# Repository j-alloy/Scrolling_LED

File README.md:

# Scrolling_LED
Simple KiCAD schemtic of a scrolling LED

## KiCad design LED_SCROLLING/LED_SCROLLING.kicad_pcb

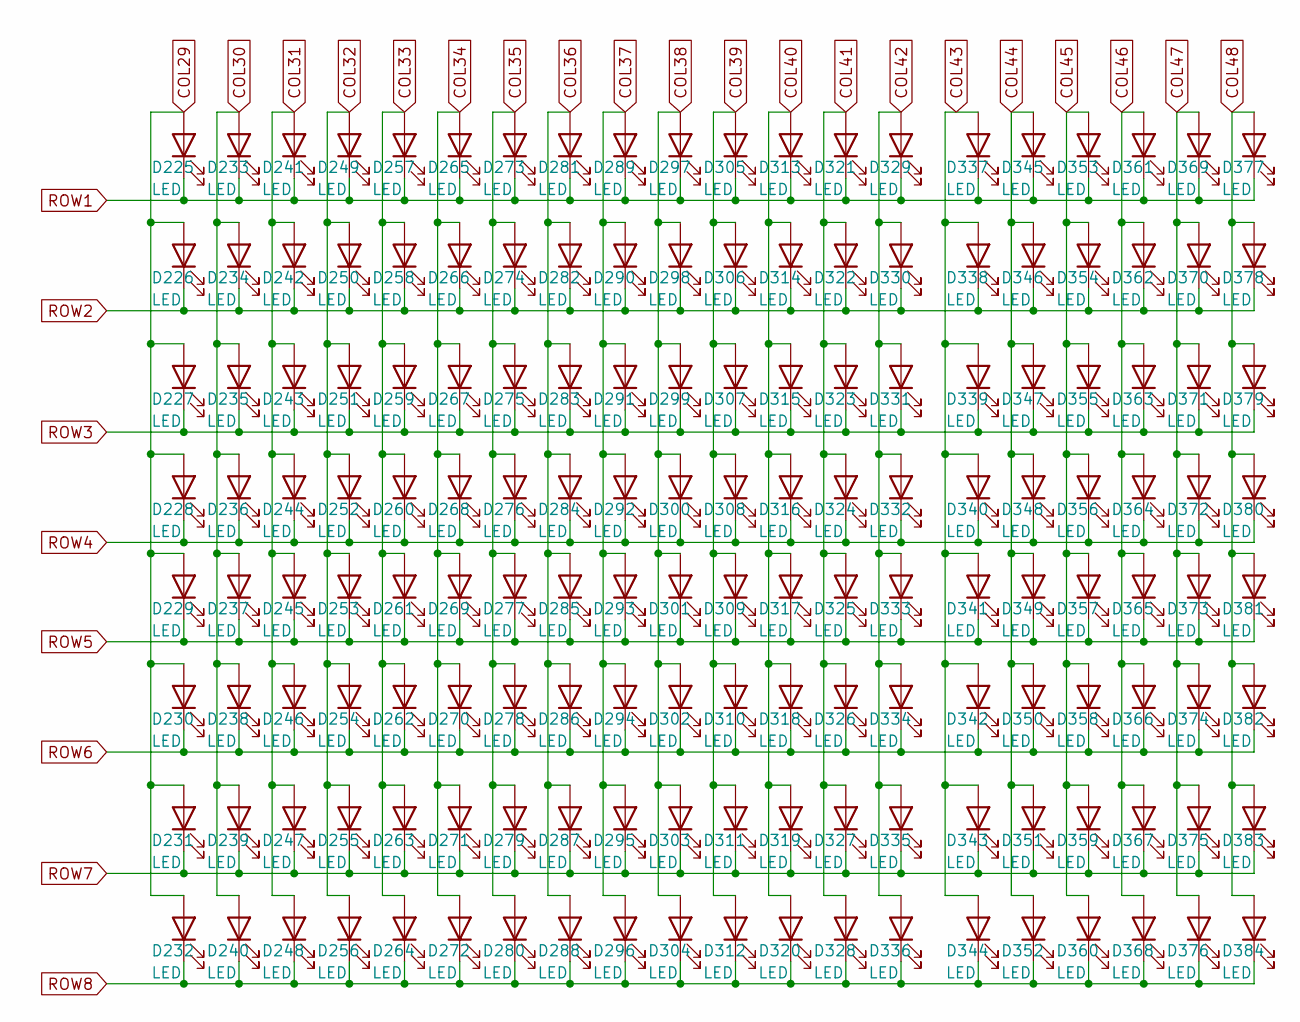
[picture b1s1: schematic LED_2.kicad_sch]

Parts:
D225, D226, D227, D228, D229, D230, D231, D232, D233, D234, D235, D236, D237, D238, D239, D240, D241, D242, D243, D244, D245, D246, D247, D248, D249, D250, D251, D252, D253, D254, D255, D256, D257, D258, D259, D260, D261, D262, D263, D264, D265, D266, D267, D268, D269, D270, D271, D272, D273, D274, D275, D276, D277, D278, D279, D280, D281, D282, D283, D284, D285, D286, D287, D288, D289, D290, D291, D292, D293, D294, D295, D296, D297, D298, D299, D300, D301, D302, D303, D304, D305, D306, D307, D308, D309, D310, D311, D312, D313, D314, D315, D316, D317, D318, D319, D320, D321, D322, D323, D324, D325, D326, D327, D328, D329, D330, D331, D332, D333, D334, D335, D336, D337, D338, D339, D340, D341, D342, D343, D344, D345, D346, D347, D348, D349, D350, D351, D352, D353, D354, D355, D356, D357, D358, D359, D360, D361, D362, D363, D364, D365, D366, D367, D368, D369, D370, D371, D372, D373, D374, D375, D376, D377, D378, D379, D380, D381, D382, D383, D384: LED; LED_0805_2012Metric

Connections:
COL29: D225.2 (A), D226.2 (A), D227.2 (A), D228.2 (A), D229.2 (A), D230.2 (A), D231.2 (A), D232.2 (A); also elsewhere on the board
COL30: D233.2 (A), D234.2 (A), D235.2 (A), D236.2 (A), D237.2 (A), D238.2 (A), D239.2 (A), D240.2 (A); also elsewhere on the board
COL31: D241.2 (A), D242.2 (A), D243.2 (A), D244.2 (A), D245.2 (A), D246.2 (A), D247.2 (A), D248.2 (A); also elsewhere on the board
COL32: D249.2 (A), D250.2 (A), D251.2 (A), D252.2 (A), D253.2 (A), D254.2 (A), D255.2 (A), D256.2 (A); also elsewhere on the board
COL33: D257.2 (A), D258.2 (A), D259.2 (A), D260.2 (A), D261.2 (A), D262.2 (A), D263.2 (A), D264.2 (A); also elsewhere on the board
COL34: D265.2 (A), D266.2 (A), D267.2 (A), D268.2 (A), D269.2 (A), D270.2 (A), D271.2 (A), D272.2 (A); also elsewhere on the board
COL35: D273.2 (A), D274.2 (A), D275.2 (A), D276.2 (A), D277.2 (A), D278.2 (A), D279.2 (A), D280.2 (A); also elsewhere on the board
COL36: D281.2 (A), D282.2 (A), D283.2 (A), D284.2 (A), D285.2 (A), D286.2 (A), D287.2 (A), D288.2 (A); also elsewhere on the board
COL37: D289.2 (A), D290.2 (A), D291.2 (A), D292.2 (A), D293.2 (A), D294.2 (A), D295.2 (A), D296.2 (A); also elsewhere on the board
COL38: D297.2 (A), D298.2 (A), D299.2 (A), D300.2 (A), D301.2 (A), D302.2 (A), D303.2 (A), D304.2 (A); also elsewhere on the board
COL39: D305.2 (A), D306.2 (A), D307.2 (A), D308.2 (A), D309.2 (A), D310.2 (A), D311.2 (A), D312.2 (A); also elsewhere on the board
COL40: D313.2 (A), D314.2 (A), D315.2 (A), D316.2 (A), D317.2 (A), D318.2 (A), D319.2 (A), D320.2 (A); also elsewhere on the board
COL41: D321.2 (A), D322.2 (A), D323.2 (A), D324.2 (A), D325.2 (A), D326.2 (A), D327.2 (A), D328.2 (A); also elsewhere on the board
COL42: D329.2 (A), D330.2 (A), D331.2 (A), D332.2 (A), D333.2 (A), D334.2 (A), D335.2 (A), D336.2 (A); also elsewhere on the board
COL43: D337.2 (A), D338.2 (A), D339.2 (A), D340.2 (A), D341.2 (A), D342.2 (A), D343.2 (A), D344.2 (A); also elsewhere on the board
COL44: D345.2 (A), D346.2 (A), D347.2 (A), D348.2 (A), D349.2 (A), D350.2 (A), D351.2 (A), D352.2 (A); also elsewhere on the board
COL45: D353.2 (A), D354.2 (A), D355.2 (A), D356.2 (A), D357.2 (A), D358.2 (A), D359.2 (A), D360.2 (A); also elsewhere on the board
COL46: D361.2 (A), D362.2 (A), D363.2 (A), D364.2 (A), D365.2 (A), D366.2 (A), D367.2 (A), D368.2 (A); also elsewhere on the board
COL47: D369.2 (A), D370.2 (A), D371.2 (A), D372.2 (A), D373.2 (A), D374.2 (A), D375.2 (A), D376.2 (A); also elsewhere on the board
COL48: D377.2 (A), D378.2 (A), D379.2 (A), D380.2 (A), D381.2 (A), D382.2 (A), D383.2 (A), D384.2 (A); also elsewhere on the board
ROW1: D225.1 (K), D233.1 (K), D241.1 (K), D249.1 (K), D257.1 (K), D265.1 (K), D273.1 (K), D281.1 (K), D289.1 (K), D297.1 (K), D305.1 (K), D313.1 (K), D321.1 (K), D329.1 (K), D337.1 (K), D345.1 (K), D353.1 (K), D361.1 (K), D369.1 (K), D377.1 (K); also elsewhere on the board
ROW2: D226.1 (K), D234.1 (K), D242.1 (K), D250.1 (K), D258.1 (K), D266.1 (K), D274.1 (K), D282.1 (K), D290.1 (K), D298.1 (K), D306.1 (K), D314.1 (K), D322.1 (K), D330.1 (K), D338.1 (K), D346.1 (K), D354.1 (K), D362.1 (K), D370.1 (K), D378.1 (K); also elsewhere on the board
ROW3: D227.1 (K), D235.1 (K), D243.1 (K), D251.1 (K), D259.1 (K), D267.1 (K), D275.1 (K), D283.1 (K), D291.1 (K), D299.1 (K), D307.1 (K), D315.1 (K), D323.1 (K), D331.1 (K), D339.1 (K), D347.1 (K), D355.1 (K), D363.1 (K), D371.1 (K), D379.1 (K); also elsewhere on the board
ROW4: D228.1 (K), D236.1 (K), D244.1 (K), D252.1 (K), D260.1 (K), D268.1 (K), D276.1 (K), D284.1 (K), D292.1 (K), D300.1 (K), D308.1 (K), D316.1 (K), D324.1 (K), D332.1 (K), D340.1 (K), D348.1 (K), D356.1 (K), D364.1 (K), D372.1 (K), D380.1 (K); also elsewhere on the board
ROW5: D229.1 (K), D237.1 (K), D245.1 (K), D253.1 (K), D261.1 (K), D269.1 (K), D277.1 (K), D285.1 (K), D293.1 (K), D301.1 (K), D309.1 (K), D317.1 (K), D325.1 (K), D333.1 (K), D341.1 (K), D349.1 (K), D357.1 (K), D365.1 (K), D373.1 (K), D381.1 (K); also elsewhere on the board
ROW6: D230.1 (K), D238.1 (K), D246.1 (K), D254.1 (K), D262.1 (K), D270.1 (K), D278.1 (K), D286.1 (K), D294.1 (K), D302.1 (K), D310.1 (K), D318.1 (K), D326.1 (K), D334.1 (K), D342.1 (K), D350.1 (K), D358.1 (K), D366.1 (K), D374.1 (K), D382.1 (K); also elsewhere on the board
ROW7: D231.1 (K), D239.1 (K), D247.1 (K), D255.1 (K), D263.1 (K), D271.1 (K), D279.1 (K), D287.1 (K), D295.1 (K), D303.1 (K), D311.1 (K), D319.1 (K), D327.1 (K), D335.1 (K), D343.1 (K), D351.1 (K), D359.1 (K), D367.1 (K), D375.1 (K), D383.1 (K); also elsewhere on the board
ROW8: D232.1 (K), D240.1 (K), D248.1 (K), D256.1 (K), D264.1 (K), D272.1 (K), D280.1 (K), D288.1 (K), D296.1 (K), D304.1 (K), D312.1 (K), D320.1 (K), D328.1 (K), D336.1 (K), D344.1 (K), D352.1 (K), D360.1 (K), D368.1 (K), D376.1 (K), D384.1 (K); also elsewhere on the board

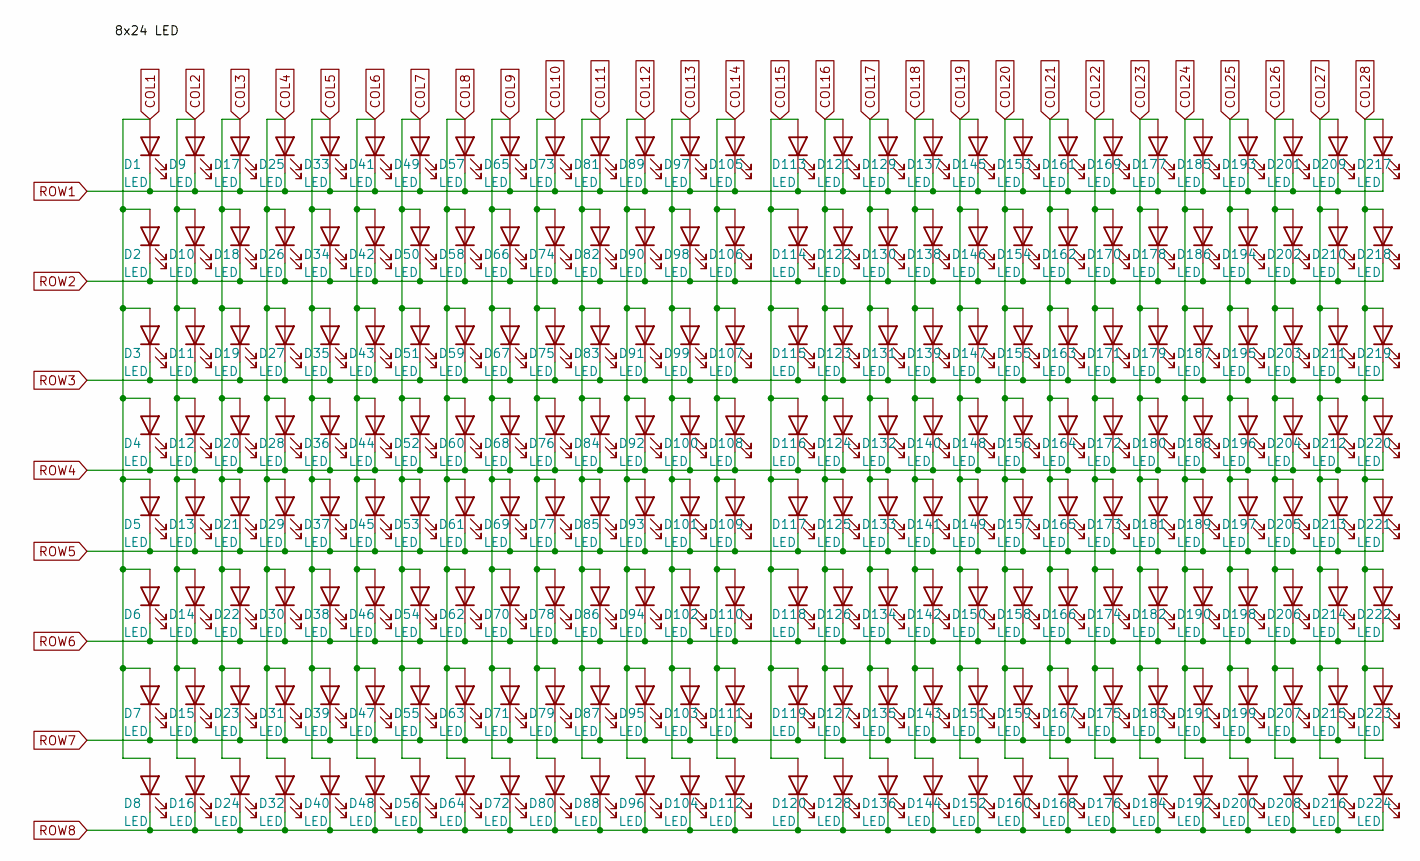
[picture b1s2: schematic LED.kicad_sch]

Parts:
D1, D2, D3, D4, D5, D6, D7, D8, D9, D10, D11, D12, D13, D14, D15, D16, D17, D18, D19, D20, D21, D22, D23, D24, D25, D26, D27, D28, D29, D30, D31, D32, D33, D34, D35, D36, D37, D38, D39, D40, D41, D42, D43, D44, D45, D46, D47, D48, D49, D50, D51, D52, D53, D54, D55, D56, D57, D58, D59, D60, D61, D62, D63, D64, D65, D66, D67, D68, D69, D70, D71, D72, D73, D74, D75, D76, D77, D78, D79, D80, D81, D82, D83, D84, D85, D86, D87, D88, D89, D90, D91, D92, D93, D94, D95, D96, D97, D98, D99, D100, D101, D102, D103, D104, D105, D106, D107, D108, D109, D110, D111, D112, D113, D114, D115, D116, D117, D118, D119, D120, D121, D122, D123, D124, D125, D126, D127, D128, D129, D130, D131, D132, D133, D134, D135, D136, D137, D138, D139, D140, D141, D142, D143, D144, D145, D146, D147, D148, D149, D150, D151, D152, D153, D154, D155, D156, D157, D158, D159, D160, D161, D162, D163, D164, D165, D166, D167, D168, D169, D170, D171, D172, D173, D174, D175, D176, D177, D178, D179, D180, D181, D182, D183, D184, D185, D186, D187, D188, D189, D190, D191, D192, D193, D194, D195, D196, D197, D198, D199, D200, D201, D202, D203, D204, D205, D206, D207, D208, D209, D210, D211, D212, D213, D214, D215, D216, D217, D218, D219, D220, D221, D222, D223, D224: LED; LED_0805_2012Metric

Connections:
COL1: D1.2 (A), D2.2 (A), D3.2 (A), D4.2 (A), D5.2 (A), D6.2 (A), D7.2 (A), D8.2 (A); also elsewhere on the board
COL2: D9.2 (A), D10.2 (A), D11.2 (A), D12.2 (A), D13.2 (A), D14.2 (A), D15.2 (A), D16.2 (A); also elsewhere on the board
COL3: D17.2 (A), D18.2 (A), D19.2 (A), D20.2 (A), D21.2 (A), D22.2 (A), D23.2 (A), D24.2 (A); also elsewhere on the board
COL4: D25.2 (A), D26.2 (A), D27.2 (A), D28.2 (A), D29.2 (A), D30.2 (A), D31.2 (A), D32.2 (A); also elsewhere on the board
COL5: D33.2 (A), D34.2 (A), D35.2 (A), D36.2 (A), D37.2 (A), D38.2 (A), D39.2 (A), D40.2 (A); also elsewhere on the board
COL6: D41.2 (A), D42.2 (A), D43.2 (A), D44.2 (A), D45.2 (A), D46.2 (A), D47.2 (A), D48.2 (A); also elsewhere on the board
COL7: D49.2 (A), D50.2 (A), D51.2 (A), D52.2 (A), D53.2 (A), D54.2 (A), D55.2 (A), D56.2 (A); also elsewhere on the board
COL8: D57.2 (A), D58.2 (A), D59.2 (A), D60.2 (A), D61.2 (A), D62.2 (A), D63.2 (A), D64.2 (A); also elsewhere on the board
COL9: D65.2 (A), D66.2 (A), D67.2 (A), D68.2 (A), D69.2 (A), D70.2 (A), D71.2 (A), D72.2 (A); also elsewhere on the board
COL10: D73.2 (A), D74.2 (A), D75.2 (A), D76.2 (A), D77.2 (A), D78.2 (A), D79.2 (A), D80.2 (A); also elsewhere on the board
COL11: D81.2 (A), D82.2 (A), D83.2 (A), D84.2 (A), D85.2 (A), D86.2 (A), D87.2 (A), D88.2 (A); also elsewhere on the board
COL12: D89.2 (A), D90.2 (A), D91.2 (A), D92.2 (A), D93.2 (A), D94.2 (A), D95.2 (A), D96.2 (A); also elsewhere on the board
COL13: D97.2 (A), D98.2 (A), D99.2 (A), D100.2 (A), D101.2 (A), D102.2 (A), D103.2 (A), D104.2 (A); also elsewhere on the board
COL14: D105.2 (A), D106.2 (A), D107.2 (A), D108.2 (A), D109.2 (A), D110.2 (A), D111.2 (A), D112.2 (A); also elsewhere on the board
COL15: D113.2 (A), D114.2 (A), D115.2 (A), D116.2 (A), D117.2 (A), D118.2 (A), D119.2 (A), D120.2 (A); also elsewhere on the board
COL16: D121.2 (A), D122.2 (A), D123.2 (A), D124.2 (A), D125.2 (A), D126.2 (A), D127.2 (A), D128.2 (A); also elsewhere on the board
COL17: D129.2 (A), D130.2 (A), D131.2 (A), D132.2 (A), D133.2 (A), D134.2 (A), D135.2 (A), D136.2 (A); also elsewhere on the board
COL18: D137.2 (A), D138.2 (A), D139.2 (A), D140.2 (A), D141.2 (A), D142.2 (A), D143.2 (A), D144.2 (A); also elsewhere on the board
COL19: D145.2 (A), D146.2 (A), D147.2 (A), D148.2 (A), D149.2 (A), D150.2 (A), D151.2 (A), D152.2 (A); also elsewhere on the board
COL20: D153.2 (A), D154.2 (A), D155.2 (A), D156.2 (A), D157.2 (A), D158.2 (A), D159.2 (A), D160.2 (A); also elsewhere on the board
COL21: D161.2 (A), D162.2 (A), D163.2 (A), D164.2 (A), D165.2 (A), D166.2 (A), D167.2 (A), D168.2 (A); also elsewhere on the board
COL22: D169.2 (A), D170.2 (A), D171.2 (A), D172.2 (A), D173.2 (A), D174.2 (A), D175.2 (A), D176.2 (A); also elsewhere on the board
COL23: D177.2 (A), D178.2 (A), D179.2 (A), D180.2 (A), D181.2 (A), D182.2 (A), D183.2 (A), D184.2 (A); also elsewhere on the board
COL24: D185.2 (A), D186.2 (A), D187.2 (A), D188.2 (A), D189.2 (A), D190.2 (A), D191.2 (A), D192.2 (A); also elsewhere on the board
COL25: D193.2 (A), D194.2 (A), D195.2 (A), D196.2 (A), D197.2 (A), D198.2 (A), D199.2 (A), D200.2 (A); also elsewhere on the board
COL26: D201.2 (A), D202.2 (A), D203.2 (A), D204.2 (A), D205.2 (A), D206.2 (A), D207.2 (A), D208.2 (A); also elsewhere on the board
COL27: D209.2 (A), D210.2 (A), D211.2 (A), D212.2 (A), D213.2 (A), D214.2 (A), D215.2 (A), D216.2 (A); also elsewhere on the board
COL28: D217.2 (A), D218.2 (A), D219.2 (A), D220.2 (A), D221.2 (A), D222.2 (A), D223.2 (A), D224.2 (A); also elsewhere on the board
ROW1: D1.1 (K), D9.1 (K), D17.1 (K), D25.1 (K), D33.1 (K), D41.1 (K), D49.1 (K), D57.1 (K), D65.1 (K), D73.1 (K), D81.1 (K), D89.1 (K), D97.1 (K), D105.1 (K), D113.1 (K), D121.1 (K), D129.1 (K), D137.1 (K), D145.1 (K), D153.1 (K), D161.1 (K), D169.1 (K), D177.1 (K), D185.1 (K), D193.1 (K), D201.1 (K), D209.1 (K), D217.1 (K); also elsewhere on the board
ROW2: D2.1 (K), D10.1 (K), D18.1 (K), D26.1 (K), D34.1 (K), D42.1 (K), D50.1 (K), D58.1 (K), D66.1 (K), D74.1 (K), D82.1 (K), D90.1 (K), D98.1 (K), D106.1 (K), D114.1 (K), D122.1 (K), D130.1 (K), D138.1 (K), D146.1 (K), D154.1 (K), D162.1 (K), D170.1 (K), D178.1 (K), D186.1 (K), D194.1 (K), D202.1 (K), D210.1 (K), D218.1 (K); also elsewhere on the board
ROW3: D3.1 (K), D11.1 (K), D19.1 (K), D27.1 (K), D35.1 (K), D43.1 (K), D51.1 (K), D59.1 (K), D67.1 (K), D75.1 (K), D83.1 (K), D91.1 (K), D99.1 (K), D107.1 (K), D115.1 (K), D123.1 (K), D131.1 (K), D139.1 (K), D147.1 (K), D155.1 (K), D163.1 (K), D171.1 (K), D179.1 (K), D187.1 (K), D195.1 (K), D203.1 (K), D211.1 (K), D219.1 (K); also elsewhere on the board
ROW4: D4.1 (K), D12.1 (K), D20.1 (K), D28.1 (K), D36.1 (K), D44.1 (K), D52.1 (K), D60.1 (K), D68.1 (K), D76.1 (K), D84.1 (K), D92.1 (K), D100.1 (K), D108.1 (K), D116.1 (K), D124.1 (K), D132.1 (K), D140.1 (K), D148.1 (K), D156.1 (K), D164.1 (K), D172.1 (K), D180.1 (K), D188.1 (K), D196.1 (K), D204.1 (K), D212.1 (K), D220.1 (K); also elsewhere on the board
ROW5: D5.1 (K), D13.1 (K), D21.1 (K), D29.1 (K), D37.1 (K), D45.1 (K), D53.1 (K), D61.1 (K), D69.1 (K), D77.1 (K), D85.1 (K), D93.1 (K), D101.1 (K), D109.1 (K), D117.1 (K), D125.1 (K), D133.1 (K), D141.1 (K), D149.1 (K), D157.1 (K), D165.1 (K), D173.1 (K), D181.1 (K), D189.1 (K), D197.1 (K), D205.1 (K), D213.1 (K), D221.1 (K); also elsewhere on the board
ROW6: D6.1 (K), D14.1 (K), D22.1 (K), D30.1 (K), D38.1 (K), D46.1 (K), D54.1 (K), D62.1 (K), D70.1 (K), D78.1 (K), D86.1 (K), D94.1 (K), D102.1 (K), D110.1 (K), D118.1 (K), D126.1 (K), D134.1 (K), D142.1 (K), D150.1 (K), D158.1 (K), D166.1 (K), D174.1 (K), D182.1 (K), D190.1 (K), D198.1 (K), D206.1 (K), D214.1 (K), D222.1 (K); also elsewhere on the board
ROW7: D7.1 (K), D15.1 (K), D23.1 (K), D31.1 (K), D39.1 (K), D47.1 (K), D55.1 (K), D63.1 (K), D71.1 (K), D79.1 (K), D87.1 (K), D95.1 (K), D103.1 (K), D111.1 (K), D119.1 (K), D127.1 (K), D135.1 (K), D143.1 (K), D151.1 (K), D159.1 (K), D167.1 (K), D175.1 (K), D183.1 (K), D191.1 (K), D199.1 (K), D207.1 (K), D215.1 (K), D223.1 (K); also elsewhere on the board
ROW8: D8.1 (K), D16.1 (K), D24.1 (K), D32.1 (K), D40.1 (K), D48.1 (K), D56.1 (K), D64.1 (K), D72.1 (K), D80.1 (K), D88.1 (K), D96.1 (K), D104.1 (K), D112.1 (K), D120.1 (K), D128.1 (K), D136.1 (K), D144.1 (K), D152.1 (K), D160.1 (K), D168.1 (K), D176.1 (K), D184.1 (K), D192.1 (K), D200.1 (K), D208.1 (K), D216.1 (K), D224.1 (K); also elsewhere on the board

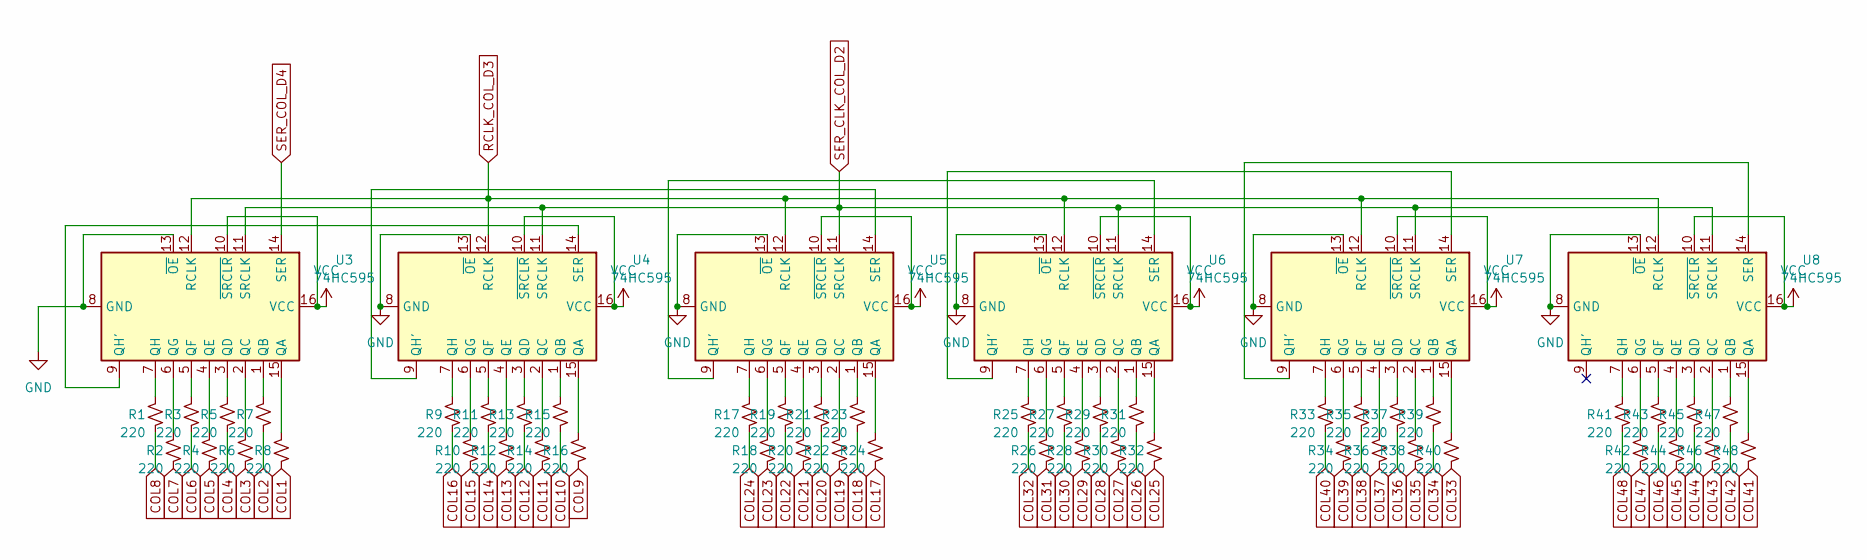
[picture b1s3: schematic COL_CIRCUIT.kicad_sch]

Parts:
R1, R2, R3, R4, R5, R6, R7, R8, R9, R10, R11, R12, R13, R14, R15, R16, R17, R18, R19, R20, R21, R22, R23, R24, R25, R26, R27, R28, R29, R30, R31, R32, R33, R34, R35, R36, R37, R38, R39, R40, R41, R42, R43, R44, R45, R46, R47, R48: 220; R_0805_2012Metric
U3, U4, U5, U6, U7, U8: 74HC595; MC74HC595ADTR2G

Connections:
COL1: R8.2; also elsewhere on the board
COL2: R7.2; also elsewhere on the board
COL3: R6.2; also elsewhere on the board
COL4: R5.2; also elsewhere on the board
COL5: R4.2; also elsewhere on the board
COL6: R3.2; also elsewhere on the board
COL7: R2.2; also elsewhere on the board
COL8: R1.2; also elsewhere on the board
COL9: R16.2; also elsewhere on the board
COL10: R15.2; also elsewhere on the board
COL11: R14.2; also elsewhere on the board
COL12: R13.2; also elsewhere on the board
COL13: R12.2; also elsewhere on the board
COL14: R11.2; also elsewhere on the board
COL15: R10.2; also elsewhere on the board
COL16: R9.2; also elsewhere on the board
COL17: R24.2; also elsewhere on the board
COL18: R23.2; also elsewhere on the board
COL19: R22.2; also elsewhere on the board
COL20: R21.2; also elsewhere on the board
COL21: R20.2; also elsewhere on the board
COL22: R19.2; also elsewhere on the board
COL23: R18.2; also elsewhere on the board
COL24: R17.2; also elsewhere on the board
COL25: R32.2; also elsewhere on the board
COL26: R31.2; also elsewhere on the board
COL27: R30.2; also elsewhere on the board
COL28: R29.2; also elsewhere on the board
COL29: R28.2; also elsewhere on the board
COL30: R27.2; also elsewhere on the board
COL31: R26.2; also elsewhere on the board
COL32: R25.2; also elsewhere on the board
COL33: R40.2; also elsewhere on the board
COL34: R39.2; also elsewhere on the board
COL35: R38.2; also elsewhere on the board
COL36: R37.2; also elsewhere on the board
COL37: R36.2; also elsewhere on the board
COL38: R35.2; also elsewhere on the board
COL39: R34.2; also elsewhere on the board
COL40: R33.2; also elsewhere on the board
COL41: R48.2; also elsewhere on the board
COL42: R47.2; also elsewhere on the board
COL43: R46.2; also elsewhere on the board
COL44: R45.2; also elsewhere on the board
COL45: R44.2; also elsewhere on the board
COL46: R43.2; also elsewhere on the board
COL47: R42.2; also elsewhere on the board
COL48: R41.2; also elsewhere on the board
GND: U3.8 (GND), U3.13 (~OE), U4.8 (GND), U4.13 (~OE), U5.8 (GND), U5.13 (~OE), U6.8 (GND), U6.13 (~OE), U7.8 (GND), U7.13 (~OE), U8.8 (GND), U8.13 (~OE); also elsewhere on the board
unnamed: R1.1, U3.7 (QH)
unnamed: R2.1, U3.6 (QG)
unnamed: R3.1, U3.5 (QF)
unnamed: R4.1, U3.4 (QE)
unnamed: R5.1, U3.3 (QD)
unnamed: R6.1, U3.2 (QC)
unnamed: R7.1, U3.1 (QB)
unnamed: R8.1, U3.15 (QA)
unnamed: R9.1, U4.7 (QH)
unnamed: R10.1, U4.6 (QG)
unnamed: R11.1, U4.5 (QF)
unnamed: R12.1, U4.4 (QE)
unnamed: R13.1, U4.3 (QD)
unnamed: R14.1, U4.2 (QC)
unnamed: R15.1, U4.1 (QB)
unnamed: R16.1, U4.15 (QA)
unnamed: R17.1, U5.7 (QH)
unnamed: R18.1, U5.6 (QG)
unnamed: R19.1, U5.5 (QF)
unnamed: R20.1, U5.4 (QE)
unnamed: R21.1, U5.3 (QD)
unnamed: R22.1, U5.2 (QC)
unnamed: R23.1, U5.1 (QB)
unnamed: R24.1, U5.15 (QA)
unnamed: R25.1, U6.7 (QH)
unnamed: R26.1, U6.6 (QG)
unnamed: R27.1, U6.5 (QF)
unnamed: R28.1, U6.4 (QE)
unnamed: R29.1, U6.3 (QD)
unnamed: R30.1, U6.2 (QC)
unnamed: R31.1, U6.1 (QB)
unnamed: R32.1, U6.15 (QA)
unnamed: R33.1, U7.7 (QH)
unnamed: R34.1, U7.6 (QG)
unnamed: R35.1, U7.5 (QF)
unnamed: R36.1, U7.4 (QE)
unnamed: R37.1, U7.3 (QD)
unnamed: R38.1, U7.2 (QC)
unnamed: R39.1, U7.1 (QB)
unnamed: R40.1, U7.15 (QA)
unnamed: R41.1, U8.7 (QH)
unnamed: R42.1, U8.6 (QG)
unnamed: R43.1, U8.5 (QF)
unnamed: R44.1, U8.4 (QE)
unnamed: R45.1, U8.3 (QD)
unnamed: R46.1, U8.2 (QC)
unnamed: R47.1, U8.1 (QB)
unnamed: R48.1, U8.15 (QA)
unnamed: U3.9 (QH'), U4.14 (SER)
unnamed: U4.9 (QH'), U5.14 (SER)
unnamed: U5.9 (QH'), U6.14 (SER)
unnamed: U6.9 (QH'), U7.14 (SER)
unnamed: U7.9 (QH'), U8.14 (SER)
RCLK_COL_D3: U3.12 (RCLK), U4.12 (RCLK), U5.12 (RCLK), U6.12 (RCLK), U7.12 (RCLK), U8.12 (RCLK)
SER_CLK_COL_D2: U3.11 (SRCLK), U4.11 (SRCLK), U5.11 (SRCLK), U6.11 (SRCLK), U7.11 (SRCLK), U8.11 (SRCLK)
SER_COL_D4: U3.14 (SER)
VCC: U3.10 (~SRCLR), U3.16 (VCC), U4.10 (~SRCLR), U4.16 (VCC), U5.10 (~SRCLR), U5.16 (VCC), U6.10 (~SRCLR), U6.16 (VCC), U7.10 (~SRCLR), U7.16 (VCC), U8.10 (~SRCLR), U8.16 (VCC); also elsewhere on the board

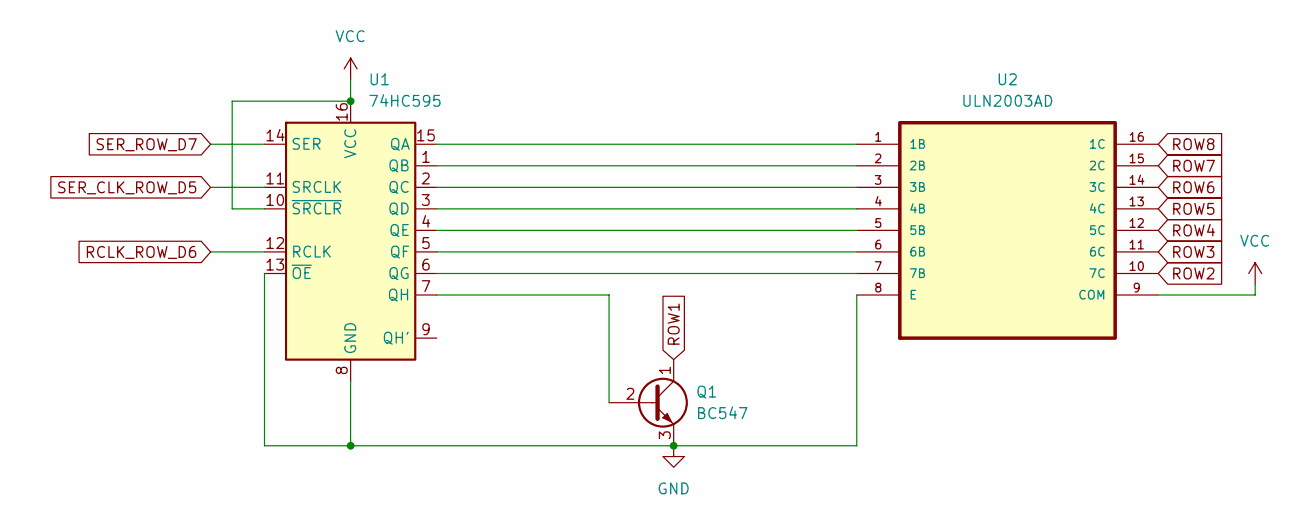
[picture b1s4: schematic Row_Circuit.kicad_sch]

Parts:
Q1: BC547; TO-92_Inline
U1: 74HC595; MC74HC595ADTR2G
U2: ULN2003AD

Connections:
GND: Q1.3 (E), U1.8 (GND), U1.13 (~OE), U2.8 (E); also elsewhere on the board
unnamed: Q1.2 (B), U1.7 (QH)
unnamed: U1.1 (QB), U2.2 (2B)
unnamed: U1.2 (QC), U2.3 (3B)
unnamed: U1.3 (QD), U2.4 (4B)
unnamed: U1.4 (QE), U2.5 (5B)
unnamed: U1.5 (QF), U2.6 (6B)
unnamed: U1.6 (QG), U2.7 (7B)
unnamed: U1.15 (QA), U2.1 (1B)
RCLK_ROW_D6: U1.12 (RCLK)
ROW1: Q1.1 (C); also elsewhere on the board
ROW2: U2.10 (7C); also elsewhere on the board
ROW3: U2.11 (6C); also elsewhere on the board
ROW4: U2.12 (5C); also elsewhere on the board
ROW5: U2.13 (4C); also elsewhere on the board
ROW6: U2.14 (3C); also elsewhere on the board
ROW7: U2.15 (2C); also elsewhere on the board
ROW8: U2.16 (1C); also elsewhere on the board
SER_CLK_ROW_D5: U1.11 (SRCLK)
SER_ROW_D7: U1.14 (SER)
VCC: U1.10 (~SRCLR), U1.16 (VCC), U2.9 (COM); also elsewhere on the board

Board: 2 copper layers, 441 parts (0 on the bottom side), 121 nets, no tracks yet.

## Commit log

2023-02-12 A-Added new KiCAD files
    Schematic of LED Scrolling without MCU
2023-02-14 Position 10% LED
